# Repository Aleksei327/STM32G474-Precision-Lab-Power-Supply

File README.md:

# Precision Programmable Laboratory Power Supply

[Русская версия](README.ru.md)

A hardware development project for a galvanically isolated, fully programmable laboratory power supply. The design combines a tracking synchronous buck preregulator with a fast linear post-regulator to provide high efficiency without giving up low output noise.

> **Development status (November 2026):** both boards are etched, assembled and powered up, and the device runs on bring-up firmware. Verified on the bench so far: the auxiliary rails, the linear post-regulator and the synchronous buck without load. Tests under load in amps, the current limit and calibration are still ahead, so the specification table below lists design targets; measured values are in [First measurements](#first-measurements). The KiCad sources published here are the August 2026 revision — fixes found during bring-up are not merged yet.

*The assembled boards on the bench: main board, auxiliary flyback board, and the display on the diagnostics page of the bring-up firmware (55 V input switched off for the photo).*

## Target specifications

| Parameter | Target / current design |
| --- | --- |
| Output voltage | 0–50 V programmable; expected practical lower limit approximately 20–50 mV |
| Voltage setting increment | approximately 0.84 mV; 1 mV user step |
| Current setting increment | 1 mA in firmware |
| Output ripple | no more than 1 mV target |
| Present transformer capability | approximately 5–6 A continuous, 8 A peak — the limiting element today |
| Pass-element thermal budget | 7 A continuous with the current heatsink and a silicone insulator; 10 A in short bursts under NTC foldback |
| Power-stage design target | up to 10 A after the transformer rewind (a mica insulator is then required on the pass FET) |
| Operating modes | CV, digital CC, programmable foldback, controlled output ramps |
| Controller | STM32G474 |
| Voltage reference and DAC | REF5025 + 16-bit DAC8830 |
| Voltage/current monitor | 20-bit INA228 with a Kelvin-connected 10 mΩ shunt |

## First measurements

Bring-up results from 9 November 2026, taken with bring-up firmware and before any calibration.

| Test | Result |
| --- | --- |
| Linear stage, 10.000 V setpoint into 1.5 kΩ | 10.088 V on the INA228, drift within ±2 mV over one minute; the +0.9 % offset is the uncalibrated reference |
| Zero setpoint | 0.003 V at the output |
| Buck stage, no load, 100 kHz, 55.6 V input | pass-FET drain voltage follows pulse length linearly from 12.5 V to 27.2 V |
| Buck switching node | clean rectangle, 58.8 V peak (about 3 V overshoot), no missed pulses |
| Buck no-load input power at 49 % pulse length | about 6.4 W, mostly inductor core loss — under investigation |

Not tested yet: load currents in amps, current metering scale, the tracking loop, current limit, short-circuit protection in operation, and output above 25 V.

## Full schematic

The schematic is an A1 sheet. Open the SVG directly for lossless zoom.

[Russian schematic](docs/images/lab-psu-schematic-ru.svg)

## Boards

Two home-etched single-sided boards: a main board of about 260 × 152 mm and an auxiliary flyback board that generates the +67 V / −5 V rails for the post-regulator. Connections that cannot be routed on one copper layer are made with 25 documented wire jumpers.

*Copper side of the etched and assembled main board.*

[More views, layout details and the conventions used → PCB page](docs/pcb.md)

## How it works

The mains front end is based on a modified 500 W ATX supply. Its active PFC stage creates an approximately 380 V DC bus, followed by a two-switch forward converter that provides galvanic isolation and an approximately 55 V secondary rail.

An STM32G474 controls a synchronous buck stage through HRTIM. The buck output tracks the requested output voltage while maintaining only about 2–2.5 V across the linear pass MOSFET. A damped C–L–C filter attenuates switching components before the OPA454-based linear post-regulator removes the remaining ripple.

A 16-bit DAC8830 and REF5025 establish the voltage setpoint. An INA228 measures terminal voltage and shunt current; firmware implements the programmable current limit and foldback characteristic. Fast short-circuit interception does not depend on that digital loop: the STM32 analog front end drives the hardware comparator and HRTIM break input, while firmware simultaneously clears the voltage DAC and opens the output relay.

The output stage also includes reverse-polarity detection, external-voltage detection before relay closure, overvoltage protection, backfeed supervision, a fuse, surge clamps, thermal monitoring, and an independent thermal relay interlock.

## Documentation

- [System architecture and protection design](docs/architecture.md)
- [Auxiliary +67 V / −5 V flyback converter](docs/auxiliary-flyback.md)
- [PCB design and boards](docs/pcb.md)
- [Русская техническая документация](README.ru.md)

## Hardware sources

The complete KiCad 10 project is in [`hardware/`](hardware/README.md): schematic, layout, the project footprint library, hand-written 3D models with the Python scripts that generate them, and the SKiDL script the netlist is built from.

⚠️ The boards are drawn for home etching: **every drill hole in the file is a 0.6 mm pilot** that is opened up by hand afterwards. Restore the real diameters before sending these files to a fab.

## License and reuse

The documentation, the schematic and the hardware design files are published under [CC BY-NC-ND 4.0](LICENSE): read them, study them, share them with attribution, but no commercial use and no publishing of modified versions. **Building a single unit for your own private use is explicitly permitted** — the exact terms are in [NOTICE.md](NOTICE.md).

**The firmware is not published.** The hardware does not run without it, so if you build this board the control software is yours to write. Firmware and a video of the working device will follow once the hardware has been built and tested.

## Author

Aleksei Subbotin — embedded electronics and power control, France / remote. Open to freelance and contract work: [github.com/Aleksei327](https://github.com/Aleksei327) · <alsubfr@hotmail.com>

## Safety

This project contains rectified mains and an approximately 380 V DC bus. It is an engineering prototype, not a certified product. Construction and testing require appropriate isolation, current limiting, discharge procedures, protective equipment, and experience with lethal-voltage power electronics.

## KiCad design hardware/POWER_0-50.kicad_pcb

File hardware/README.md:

# Hardware sources

[Русская версия](README.ru.md) · [Back to the project overview](../README.md)

KiCad 10 project for the 0–50 V precision laboratory power supply. Open `POWER_0-50.kicad_pro`; the project-local footprint library resolves through `${KIPRJMOD}`, so no global library setup is needed.

> **Work in progress, published as-is.** The schematic and the layout are complete for this revision, but no board has been built or tested. Expect to find mistakes, and read [`docs/pcb.md`](../docs/pcb.md) before reusing anything — in particular the 0.6 mm pilot-hole convention, which will ruin a fab order if left as it is.

## Files

| Path | What it is |
| --- | --- |
| `POWER_0-50.kicad_sch` | schematic, single sheet (A1) |
| `POWER_0-50.kicad_pcb` | layout: 2 boards, 207 footprints, single-sided copper plus wire jumpers |
| `Library.pretty/` | 21 project footprints (see below) |
| `Library.3dshapes/` | 16 hand-written 3D models plus the Python generators that produce them |
| `netlist/lab_psu_skidl.py` | SKiDL script that generates the netlist — the electrical source of truth |
| `netlist/lab_psu.net` | generated netlist, the reference the schematic and the PCB are checked against |
| `netlist/lab_psu_chips.kicad_sym` | symbols for the parts KiCad does not ship |
| `jumper-wires.txt` | assembly list of the 25 wire jumpers with coordinates and lengths |

## Project footprint library

Everything that is either not in the stock libraries or had to be adapted for hand assembly:

- **Modules:** WeAct STM32G474CEU6 core board, Adafruit-style INA228 breakout (its screw terminal shares pad numbers with the header pins, so a wire can be soldered to whichever is convenient).
- **HSOP-8 with exposed pad, hand-solder pads:** `UCC27211` (EP → GND), `MP9486A` (EP → GND), `OPA454` (**EP → V− = −5 V**, not ground — see the datasheet).
- **Mechanical parts as real footprints:** three heatsinks, the constantan shunt staple, the flyback transformer on its measured bobbin, relays, the wound toroids, a THT NTC.
- Wide-pad SOIC-8/16 variants and various through-hole passives for parts that dissipate more than an SMD package can take.

## 3D models

KiCad 10 ships only STEP models, and several stock footprints in this project reference STEP files that are not in the distribution at all. The missing parts were modelled by hand as VRML and are generated by the scripts in `Library.3dshapes/_generators/`:

```
python wrlgen.py    # primitives, heatsinks, wound toroids, relays
python wrlgen2.py   # module boards, flyback transformer, NTC, SMD inductor
python wrlgen3.py   # fuse holder, connectors, shunt staple
python stand.py R21,J6   # preview rig: copies the board, keeps only the named parts
```

Two things worth knowing if you edit them: one VRML unit is 2.54 mm, the model Y axis is the negative of the board Y axis, and **KiCad's VRML loader does not draw the built-in `Cylinder` primitive at all** — every round shape here is an explicit `IndexedFaceSet` mesh.

## Netlist generator

The schematic was not drawn by hand first: `netlist/lab_psu_skidl.py` builds the circuit in SKiDL, and the resulting netlist is the reference that both the schematic and the board are verified against. If you change the circuit there, note that new parts must be appended at the **end** of the script — inserting them in the middle renumbers every later reference designator and silently desynchronises the board.

## Firmware

Not included. The firmware is not published yet, and this hardware does not operate without it — see [NOTICE.md](../NOTICE.md).

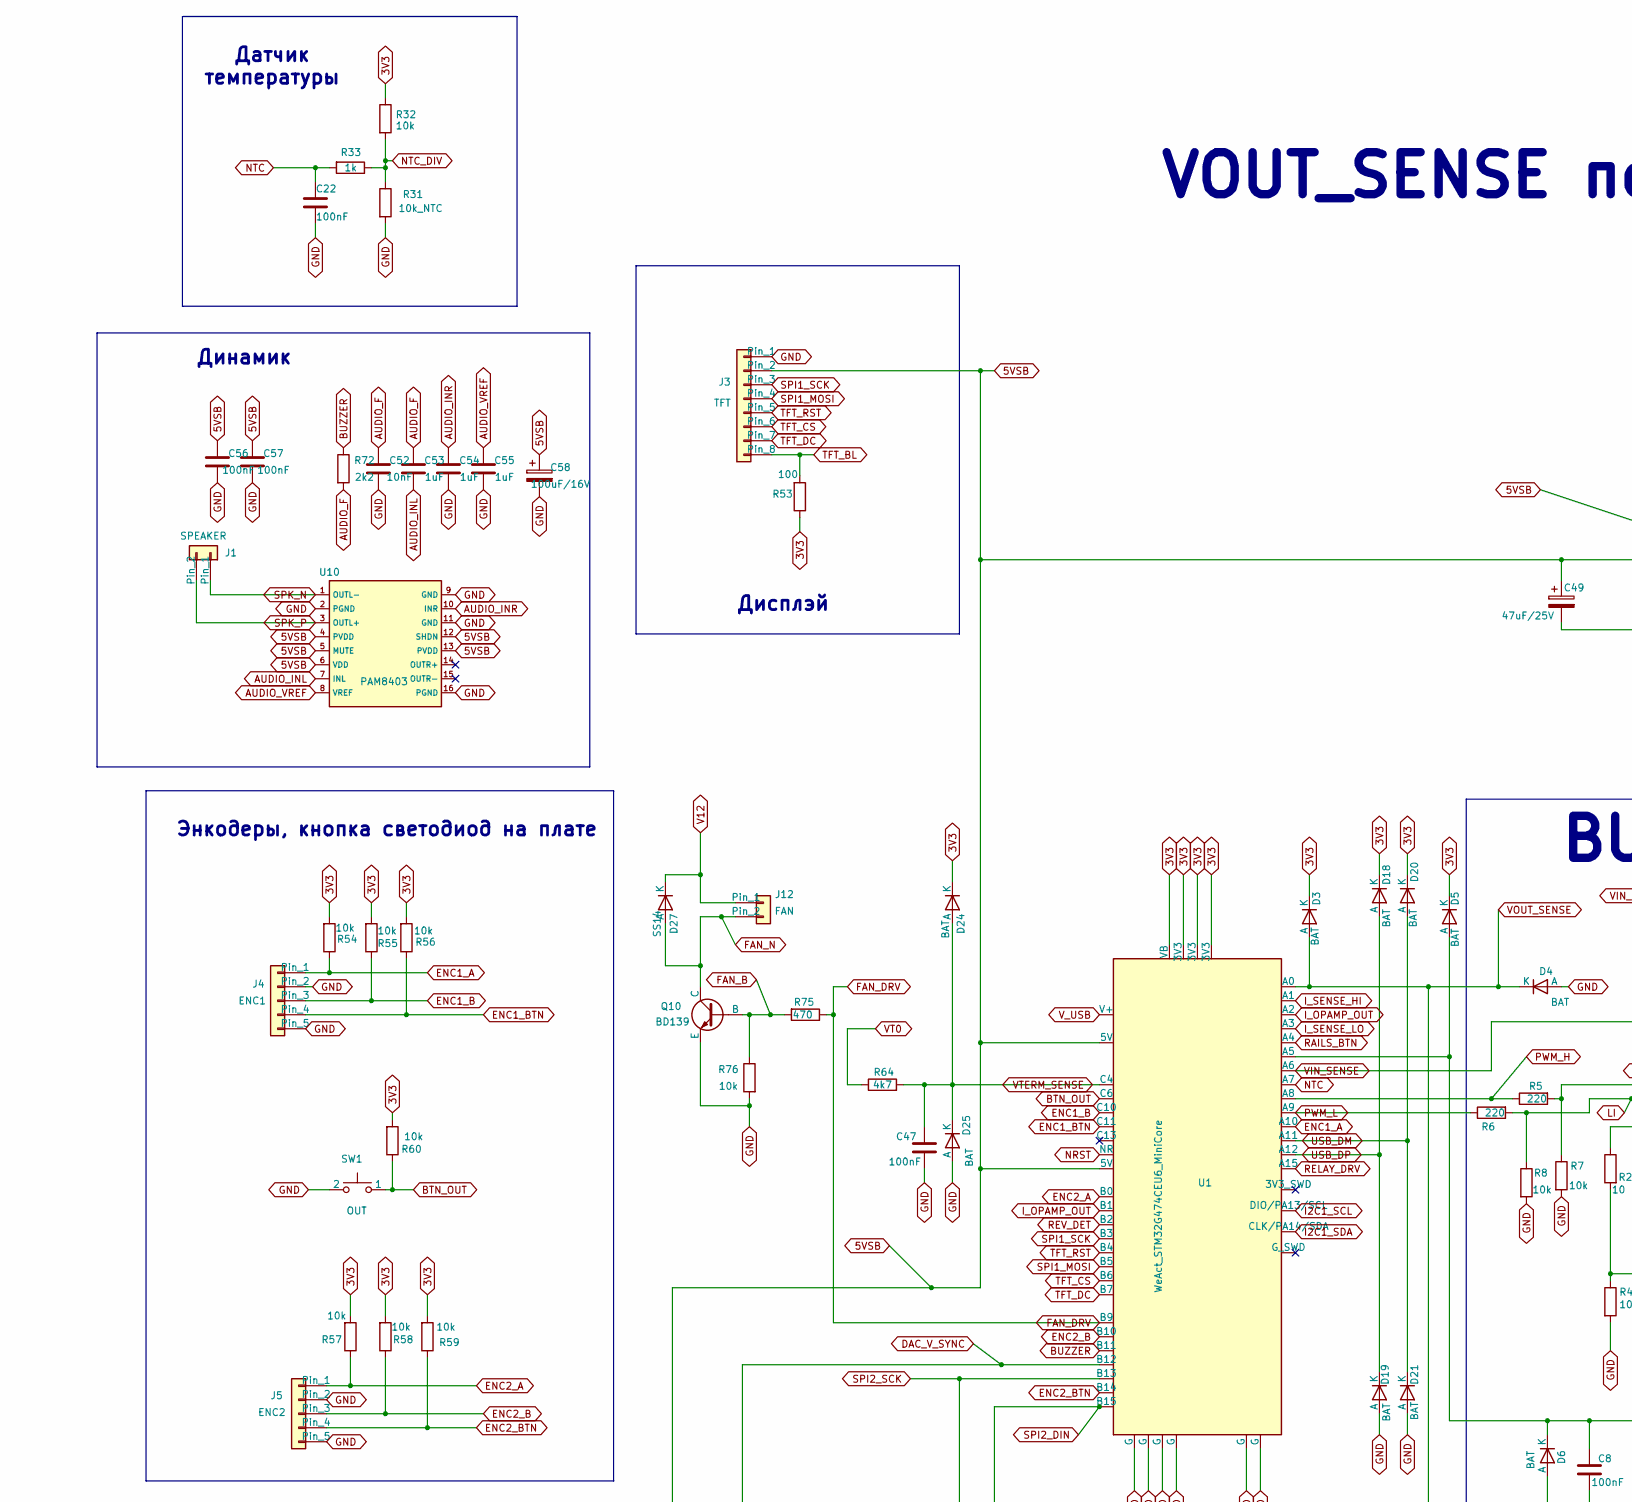
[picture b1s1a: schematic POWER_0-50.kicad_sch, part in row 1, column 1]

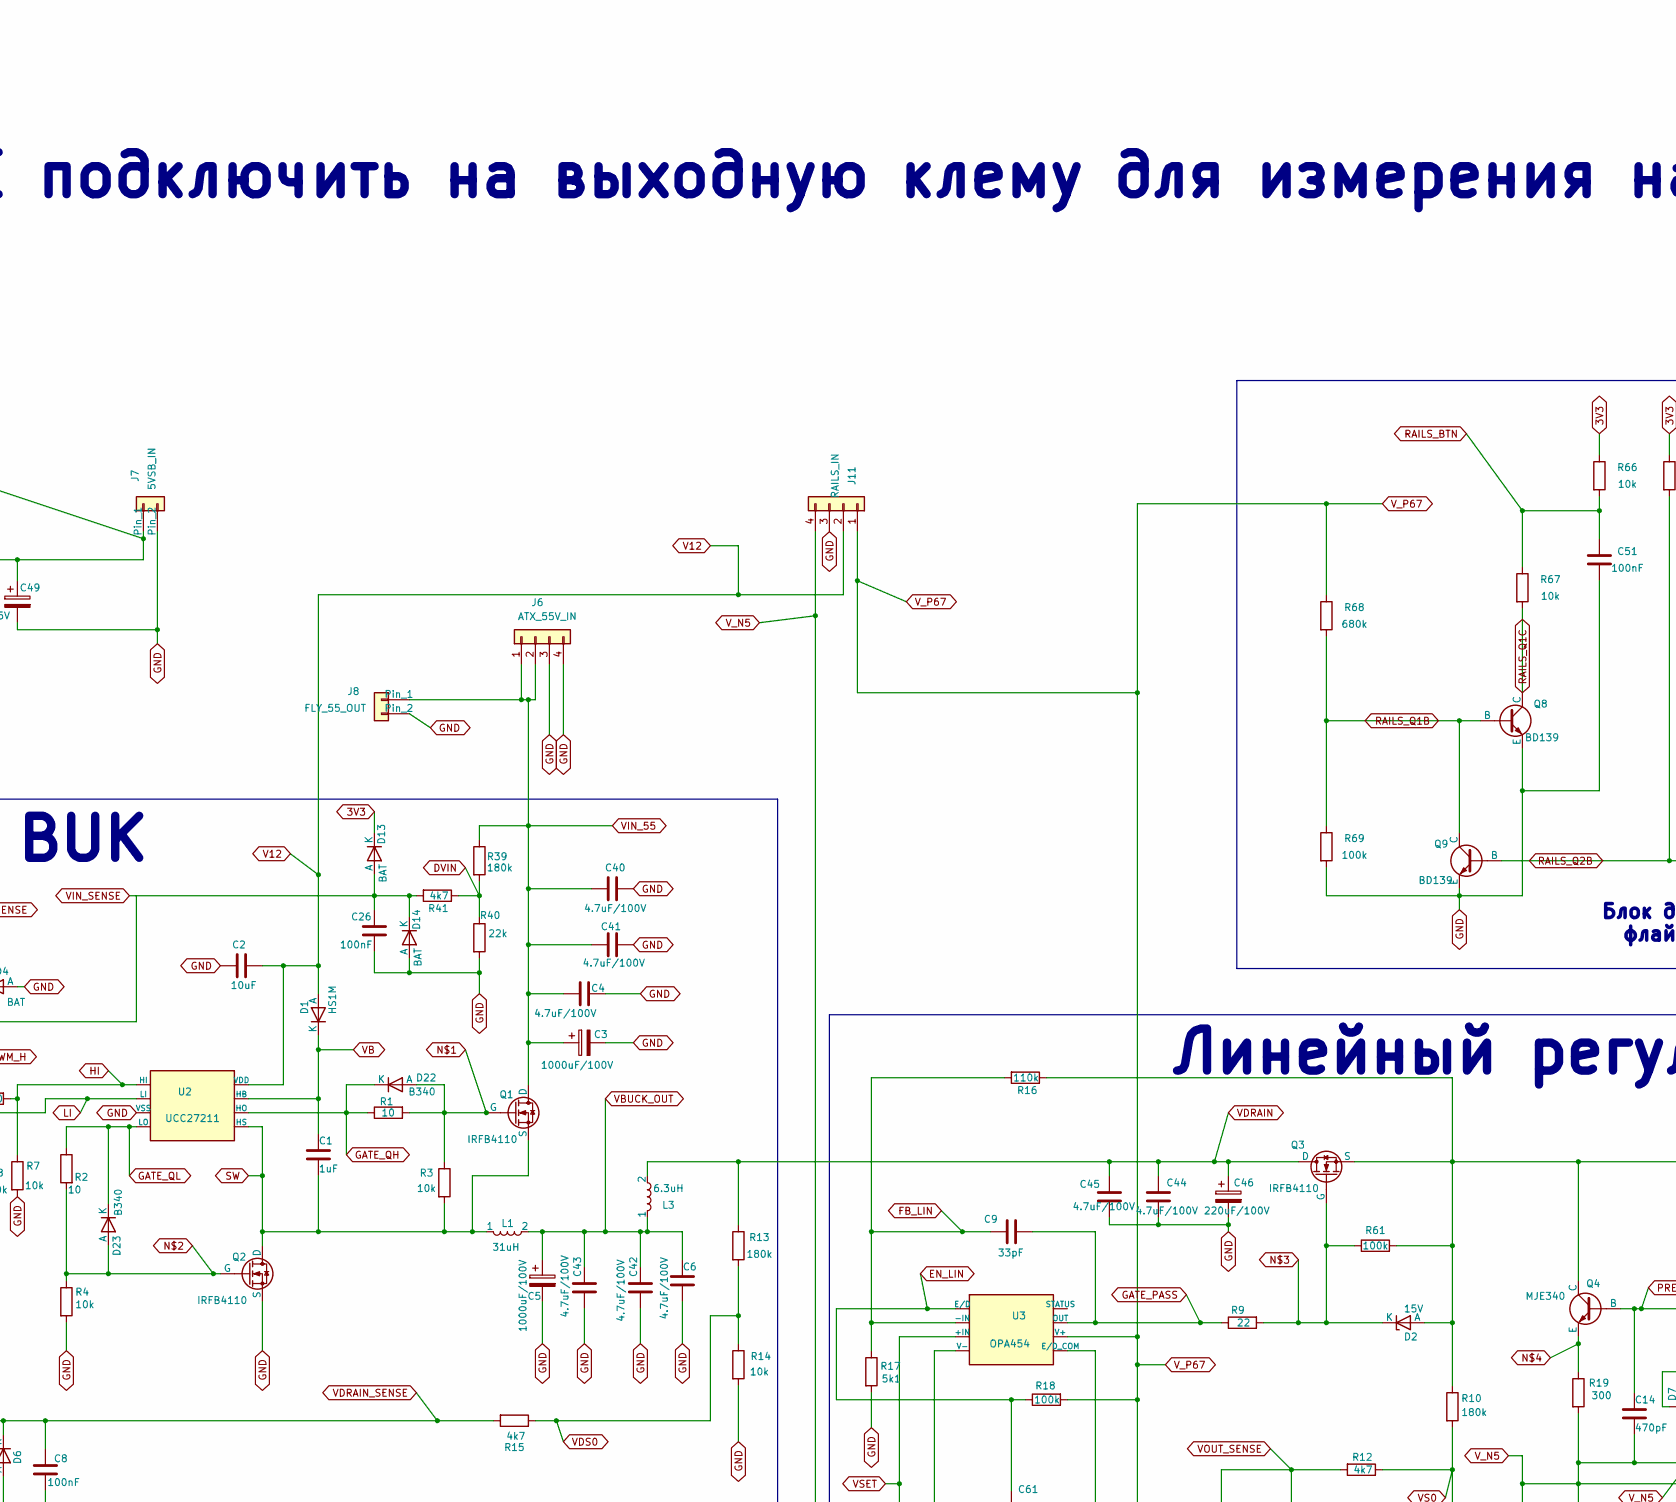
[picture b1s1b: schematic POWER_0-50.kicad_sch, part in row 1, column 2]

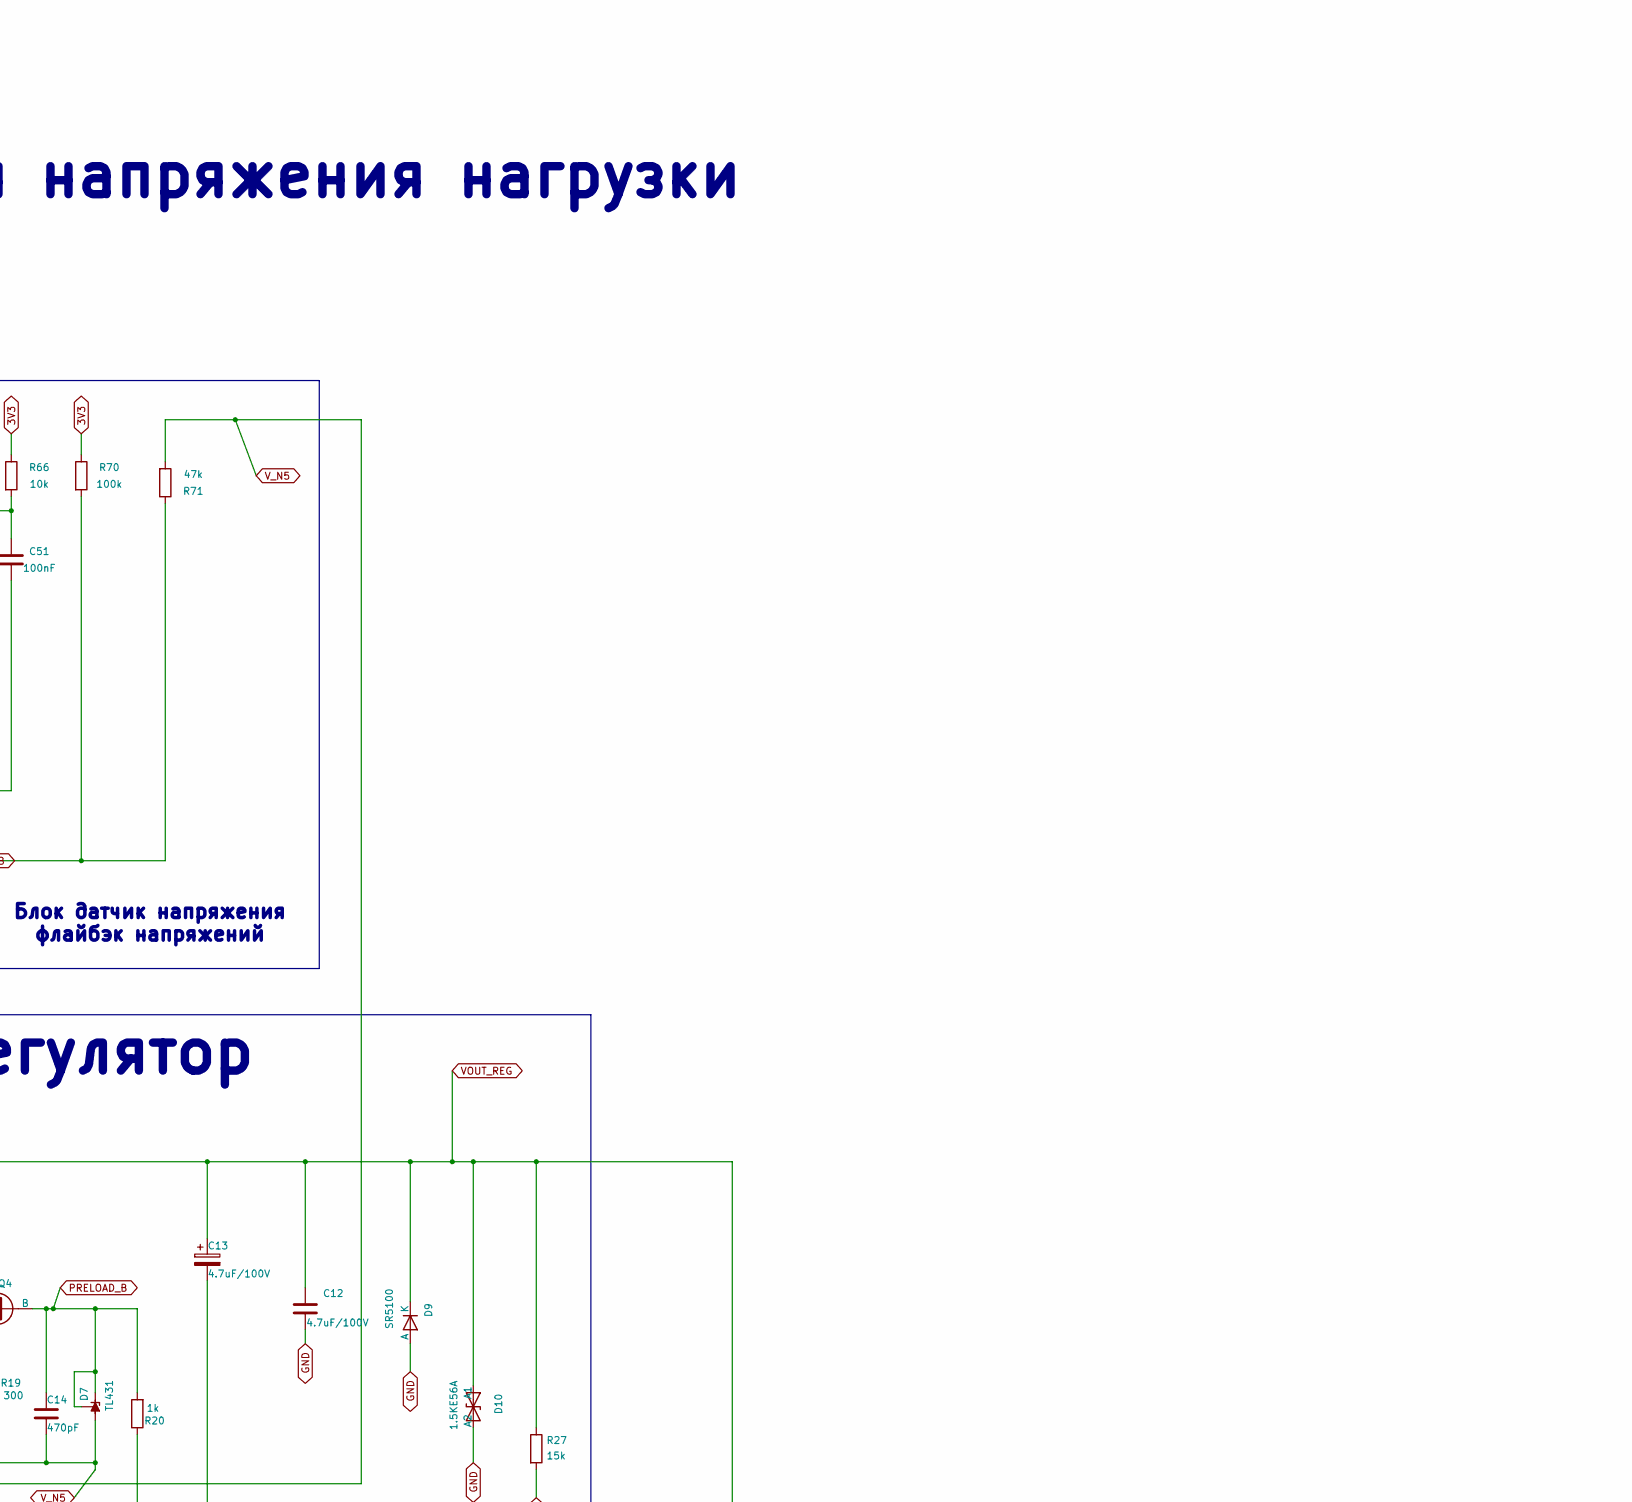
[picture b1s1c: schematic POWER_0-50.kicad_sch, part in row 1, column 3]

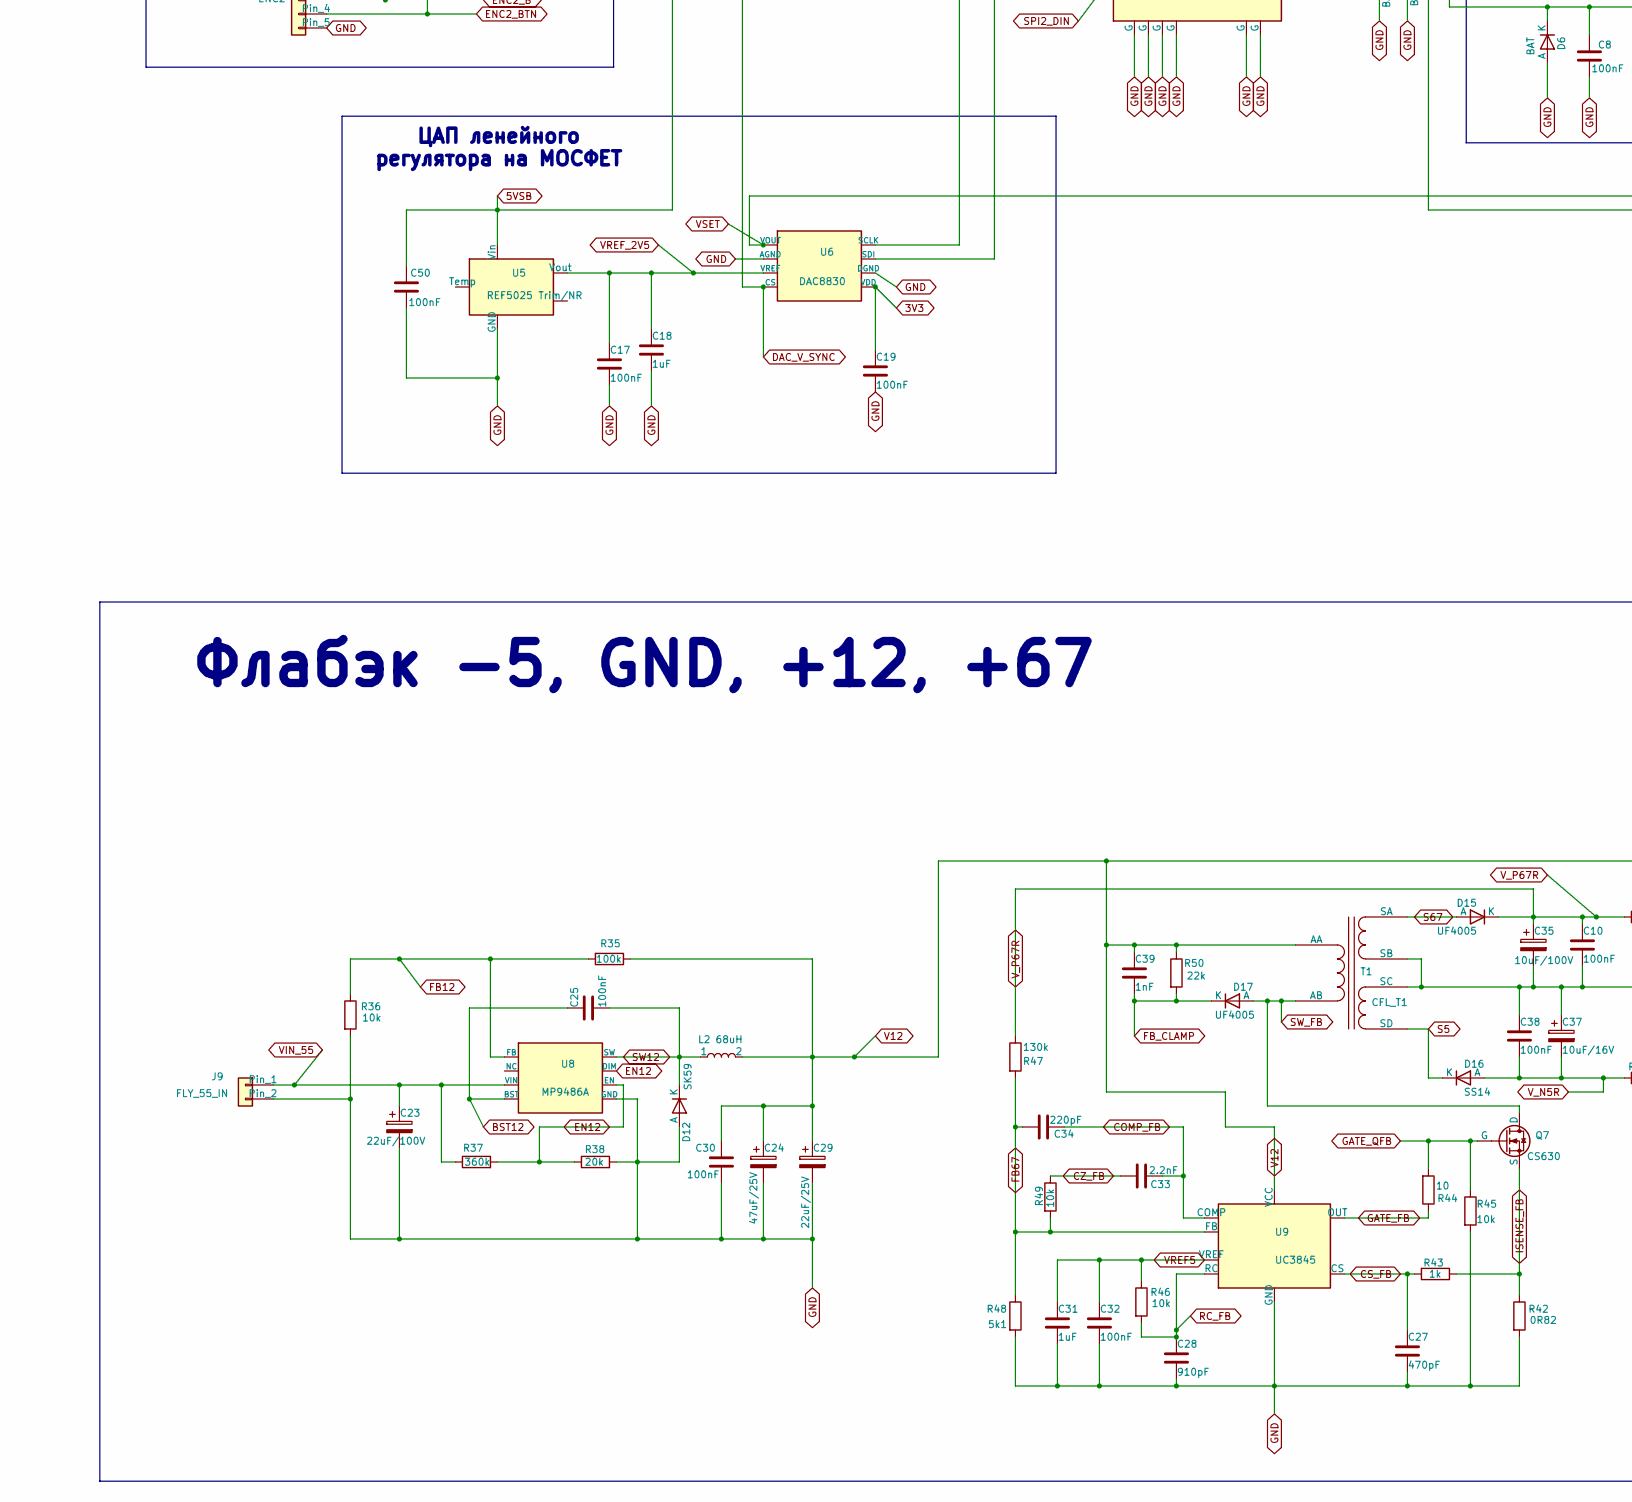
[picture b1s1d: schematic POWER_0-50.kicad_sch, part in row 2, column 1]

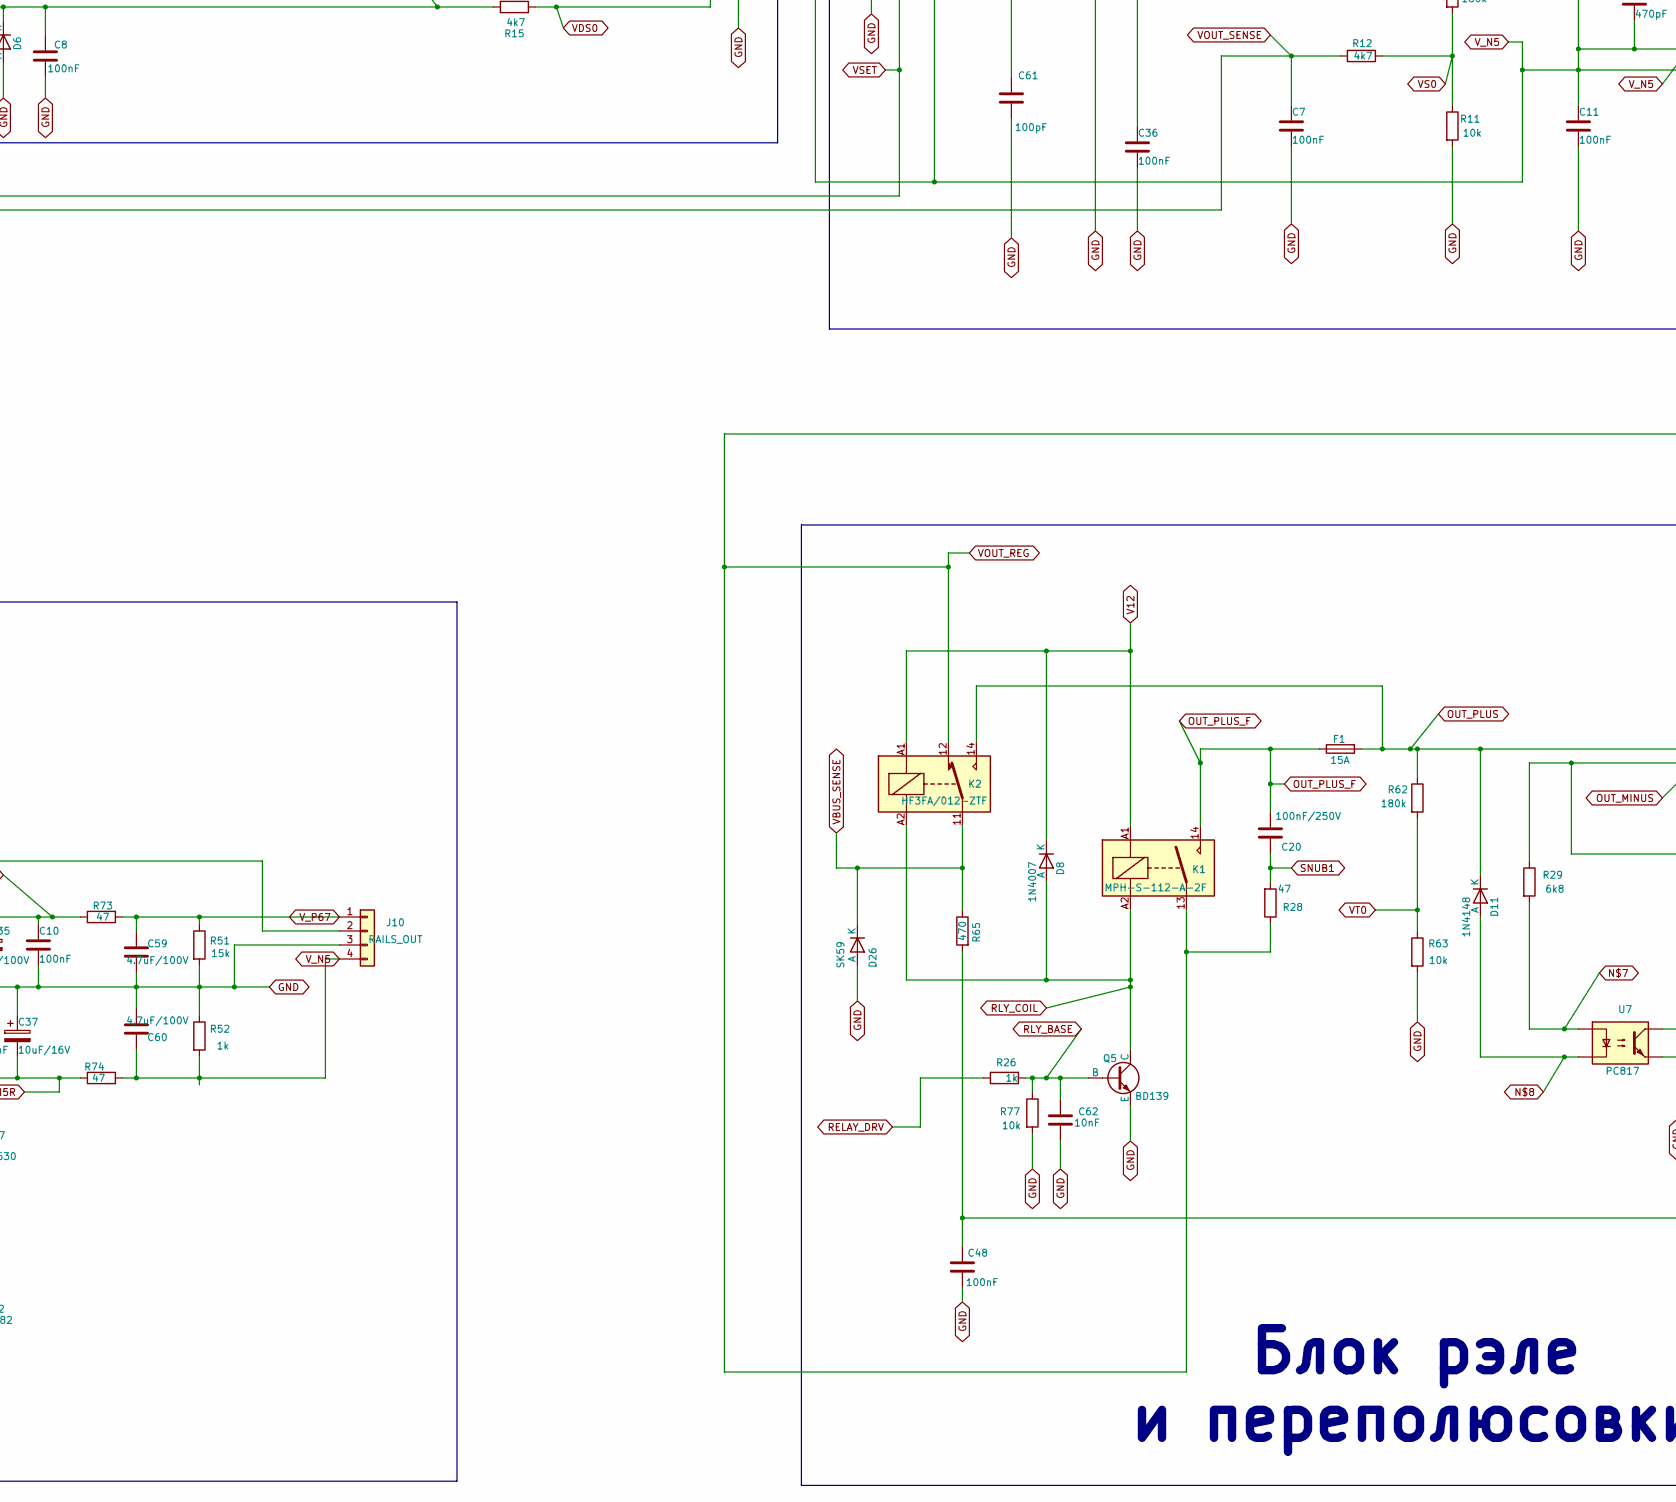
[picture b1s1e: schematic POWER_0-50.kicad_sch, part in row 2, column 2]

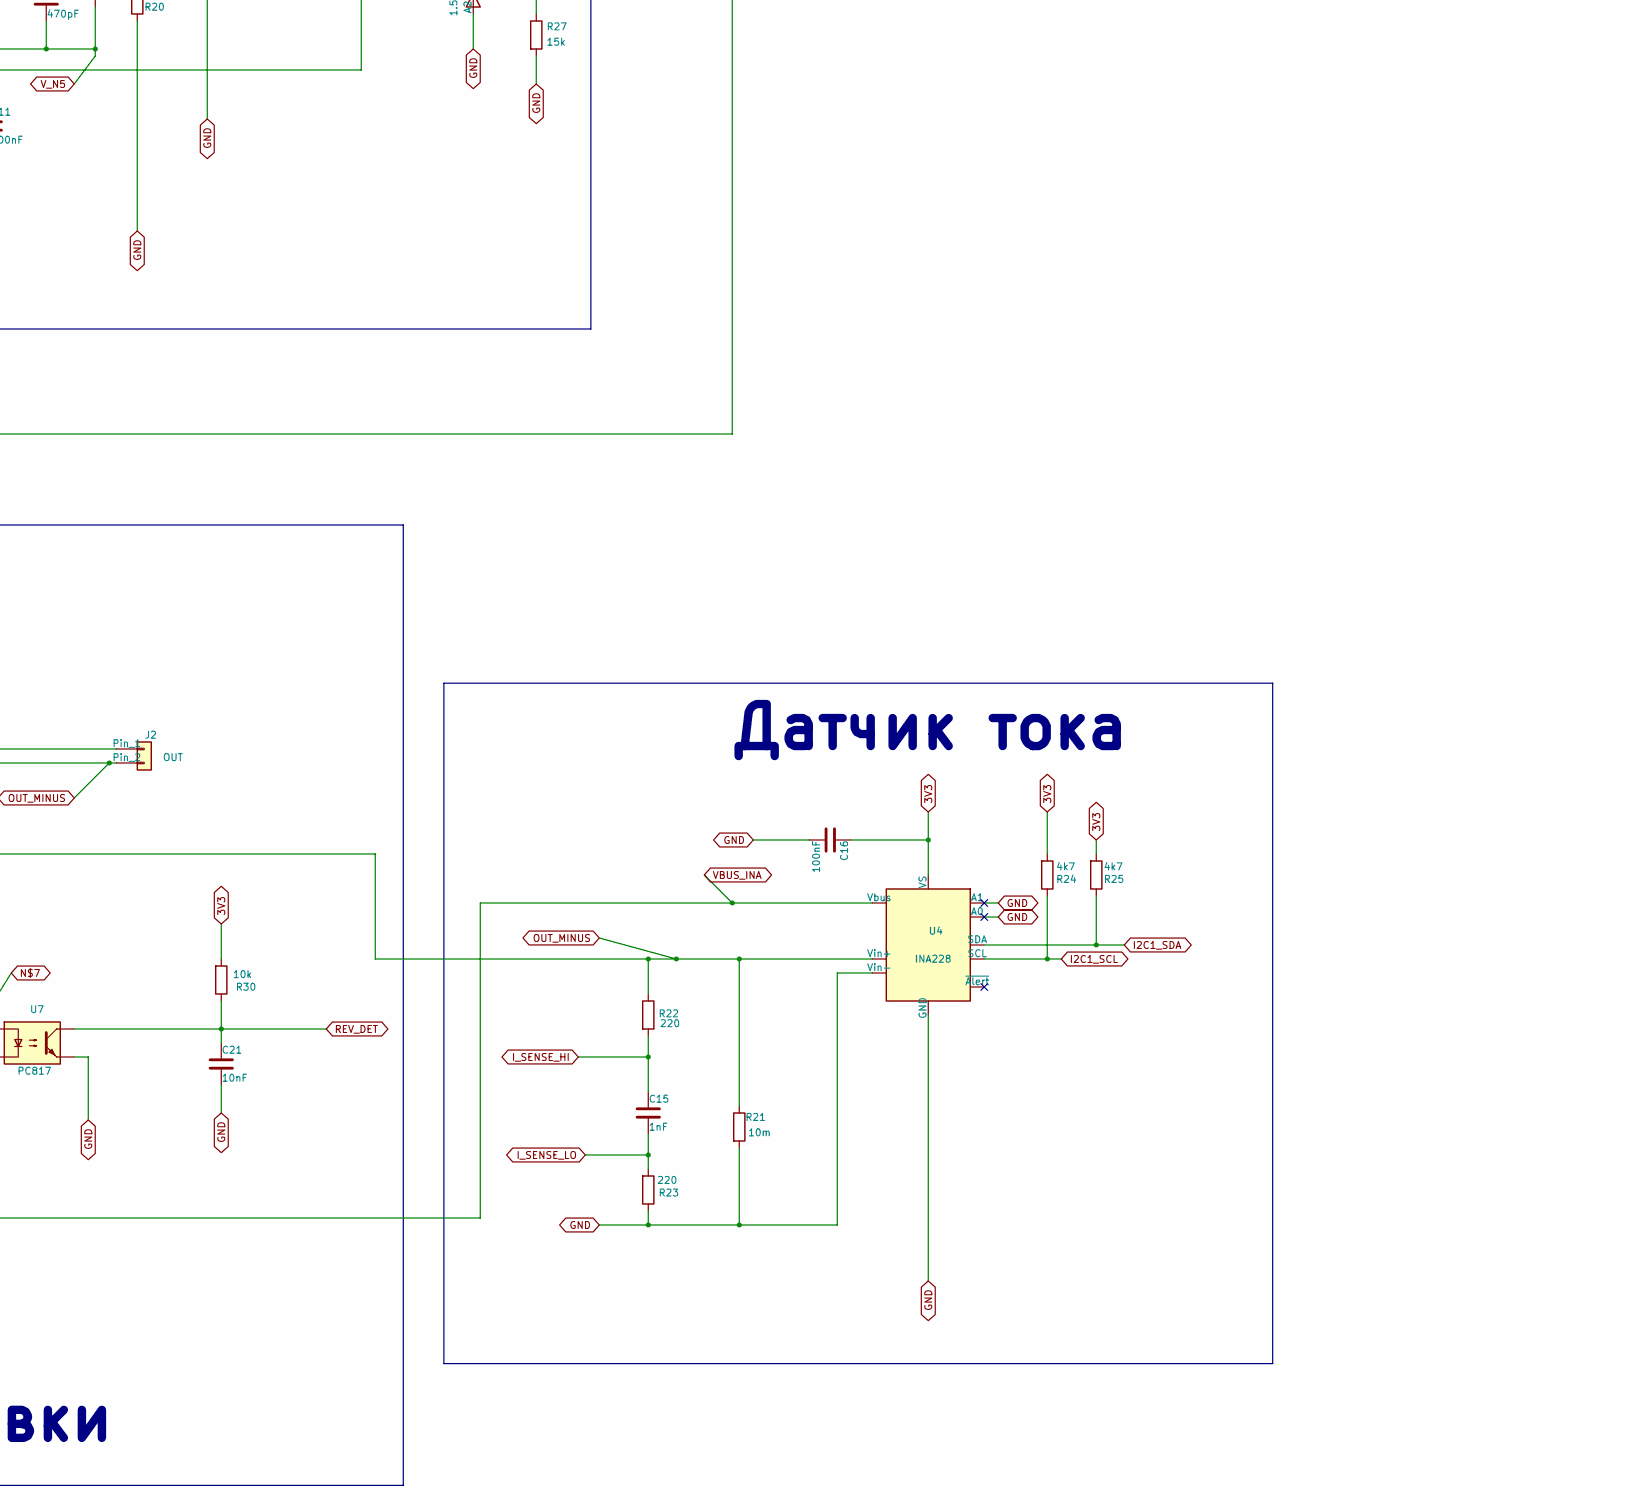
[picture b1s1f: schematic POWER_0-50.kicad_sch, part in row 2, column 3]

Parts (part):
C1, C18, C31, C53, C54, C55: 1uF; C_1206_3216Metric
C2: 10uF; C_1206_3216Metric
C3, C5: 1000uF/100V; CP_Radial_D18.0mm_P7.50mm
C4, C6, C12, C13, C40, C41, C42, C43, C44, C45, C59, C60: 4.7uF/100V; C_1206_3216Metric
C7, C8, C10, C11, C16, C17, C19, C22, C25, C26, C30, C32, C36, C38, C47, C48, C50, C51, C56, C57: 100nF; C_1206_3216Metric
C9: 33pF; C_1206_3216Metric
C14, C27: 470pF; C_1206_3216Metric
C15, C39: 1nF; C_1206_3216Metric
C20: 100nF/250V; C_1206_3216Metric
C21, C52, C62: 10nF; C_1206_3216Metric
C23: 22uF/100V; CP_Radial_D10.0mm_P5.00mm
C24, C49: 47uF/25V; CP_Radial_D10.0mm_P5.00mm
C28: 910pF; C_1206_3216Metric
C29: 22uF/25V; CP_Radial_D10.0mm_P5.00mm
C33: 2.2nF; C_1206_3216Metric
C34: 220pF; C_1206_3216Metric
C35: 10uF/100V; CP_Radial_D10.0mm_P5.00mm
C37: 10uF/16V; CP_Radial_D10.0mm_P5.00mm
C46: 220uF/100V; CP_Radial_D13.0mm_P5.00mm
C58: 100uF/16V; CP_Radial_D10.0mm_P5.00mm
C61: 100pF; C_1206_3216Metric
D1: HS1M; D_SMA
D2: 15V; D_DO-35_SOD27_P10.16mm_Horizontal
D3, D4, D5, D6, D13, D14, D18, D19, D20, D21, D24, D25: BAT; D_SOD-323_HandSolder
D7: TL431; TO-126-3_Vertical
D8: 1N4007; D_DO-201AD_P15.24mm_Horizontal
D9: SR5100; D_DO-201AD_P15.24mm_Horizontal
D10: 1.5KE56A; D_DO-201AD_P15.24mm_Horizontal
D11: 1N4148; D_DO-35_SOD27_P10.16mm_Horizontal
D12, D26: SK59; D_SMC
D15, D17: UF4005; D_DO-41_SOD81_P10.16mm_Horizontal
D16, D27: SS14; D_SMA
D22, D23: B340; D_SMC
F1: 15A; Fuseholder_Clip-5x20mm_Littelfuse_100_Inline_P20.50x4.60mm_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
J1: SPEAKER; PinHeader_1x02_P2.54mm_Vertical
J2: OUT; TerminalBlock_MaiXu_MX126-5.0-02P_1x02_P5.00mm
J3: TFT; PinHeader_1x08_P2.54mm_Vertical
J4: ENC1; PinHeader_1x05_P2.54mm_Vertical
J5: ENC2; PinHeader_1x05_P2.54mm_Vertical
J6: ATX_55V_IN; Molex_KK-396_A-41791-0004_1x04_P3.96mm_Vertical
J7: 5VSB_IN; PinHeader_1x02_P2.54mm_Vertical
J8: FLY_55_OUT; PinHeader_1x02_P2.54mm_Vertical
J9: FLY_55_IN; Conn_FLY55_JST_EH_1x03_P2.5_pins13
J10: RAILS_OUT; Conn_RAILS_1x04_P2.54_D0.6
J11: RAILS_IN; PinSocket_1x04_P2.54mm_Vertical
J12: FAN; PinHeader_1x02_P2.54mm_Vertical
K1: MPH-S-112-A-2F; Relay_MPH_1A
K2: HF3FA/012-ZTF; Relay_HF3FA_1C
L1: 31uH; L_Toroid_Vertical_Core25x10mm_P14.00mm_D1.8mm
L2: 68uH; L_SMD_15x15mm
L3: 6.3uH; L_Toroid_Vertical_Core21x7mm_P10.00mm_D2.0mm
Q1, Q2, Q3: IRFB4110; TO-220-3_Vertical
Q4: MJE340; TO-126-3_Vertical
Q5, Q8, Q9, Q10: BD139; TO-126-3_Vertical
Q7: CS630; TO-252-2
R1, R2: 10; R_2512_6332Metric
R3, R4, R7, R8, R11, R14, R30, R32, R36, R45, R46, R49, R54, R55, R56, R57, R58, R59, R60, R63, R66, R67, R76, R77: 10k; R_1206_3216Metric
R5, R6, R22, R23: 220; R_1206_3216Metric
R9: 22; R_Axial_DIN0207_L6.3mm_D2.5mm_P10.16mm_Horizontal
R10, R13, R39, R62: 180k; R_1206_3216Metric
R12, R15, R24, R25, R41, R64: 4k7; R_1206_3216Metric
R16: 110k; R_0805_2012Metric
R17: 5k1; R_0805_2012Metric
R18, R35, R61, R69, R70: 100k; R_1206_3216Metric
R19: 300; R_1206_3216Metric
R20, R26, R33, R43, R52: 1k; R_1206_3216Metric
R21: 10m; Shunt_Constantan_Staple_P20mm
R27, R51: 15k; R_Axial_DIN0207_L6.3mm_D2.5mm_P10.16mm_Horizontal
R28: 47; R_Axial_DIN0207_L6.3mm_D2.5mm_P10.16mm_Horizontal
R29: 6k8; R_Axial_DIN0207_L6.3mm_D2.5mm_P10.16mm_Horizontal
R31: 10k_NTC; NTC_THT_P7.00mm_Pad2.0mm_D0.6mm
R37: 360k; R_1206_3216Metric
R38: 20k; R_1206_3216Metric
R40, R50: 22k; R_1206_3216Metric
R42: 0R82; R_Axial_DIN0411_L9.9mm_D3.6mm_P12.70mm_Horizontal
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
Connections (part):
3V3: C16.1, C19.1, D3.1 (K), D5.1 (K), D13.1 (K), D18.1 (K), D20.1 (K), D24.1 (K), R24.2, R25.2, R30.2, R32.1, R53.1, R54.2, R55.2, R56.2, R57.2, R58.2, R59.2, R60.2, R66.1, R70.1, U1.3 (3V3), U1.4 (3V3), U1.22 (VB), U1.23 (3V3), U4.6 (VS), U6.8 (VDD)
5VSB: C49.1, C50.1, C56.1, C57.1, C58.1, J3.2, J7.1, U1.27 (5V), U1.28 (5V), U5.2 (Vin), U10.4 (PVDD), U10.5 (MUTE), U10.6 (VDD), U10.12 (SHDN), U10.13 (PVDD)
AUDIO_F: C52.1, C53.1, R72.2
AUDIO_INL: C53.2, U10.7 (INL)
AUDIO_INR: C54.1, U10.10 (INR)
AUDIO_VREF: C55.1, U10.8 (VREF)
BST12: C25.1, U8.4 (BST)
BTN_OUT: R60.1, SW1.1, U1.33 (C6)
BUZZER: R72.1, U1.5 (B11)
COMP_FB: C33.1, C34.1, U9.1 (COMP)
CS_FB: C27.1, R43.2, U9.3 (CS)
CZ_FB: C33.2, R49.1
DAC_V_SYNC: U1.29 (B12), U6.4 (CS)
DVIN: R39.2, R40.1, R41.1
EN12: R37.2, R38.1, U8.6 (DIM), U8.7 (EN)
ENC1_A: J4.1, R54.1, U1.36 (A10)
ENC1_B: J4.3, R55.1, U1.40 (C10)
ENC1_BTN: J4.4, R56.1, U1.41 (C11)
ENC2_A: J5.1, R57.1, U1.10 (B0)
ENC2_B: J5.3, R58.1, U1.6 (B10)
ENC2_BTN: J5.4, R59.1, U1.31 (B14)
EN_LIN: C61.1, R18.1, U3.8 (E/D)
FAN_B: Q10.3 (B), R75.2, R76.1
FAN_DRV: R75.1, U1.47 (B9)
FAN_N: D27.2 (A), J12.2, Q10.2 (C)
FB12: R35.2, R36.1, U8.1 (FB)
FB67: C34.2, R47.2, R48.1, R49.2, U9.2 (FB)
FB_CLAMP: C39.2, D17.1 (K), R50.2
FB_LIN: C9.2, R16.2, R17.1, U3.2 (-IN)
GATE_FB: R44.1, U9.6 (OUT)
GATE_PASS: C9.1, R9.1, U3.6 (OUT)
GATE_QFB: Q7.1 (G), R44.2, R45.1
GATE_QH: D22.1 (K), R1.1, U2.3 (HO)
GATE_QL: D23.1 (K), R2.1, U2.8 (LO)
GND: C2.2, C3.2, C4.2, C5.2, C6.2, C7.2, C8.2, C10.2, C11.2, C12.2, C13.2, C16.2, C17.2, C18.2, C19.2, C21.2, C22.2, C23.2, C24.2, C26.2, C27.2, C28.2, C29.2, C30.2, C31.2, C32.2, C35.2, C36.2, C37.1, C38.1, C40.2, C41.2, C42.2, C43.2, C44.2, C45.2, C46.2, C47.2, C48.2, C49.2, C50.2, C51.2, C52.2, C54.2, C55.2, C56.2, C57.2, C58.2, C59.2, C60.2, C61.2, C62.2, D4.2 (A), D6.2 (A), D9.2 (A), D10.2 (A2), D12.2 (A), D14.2 (A), D19.2 (A), D21.2 (A), D25.2 (A), D26.2 (A), J3.1, J4.2, J4.5, J5.2, J5.5, J6.3, J6.4, J7.2, J8.2, J9.2, J10.3, J11.3, Q2.3 (S), Q5.1 (E), Q8.1 (E), Q9.1 (E), Q10.1 (E), R4.2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
HI: R5.2, R7.1, U2.5 (HI)
I2C1_SCL: R24.1, U1.DIO (DIO/PA13/SCL), U4.5 (SCL)
I2C1_SDA: R25.1, U1.CLK (CLK/PA14/SDA), U4.4 (SDA)
ISENSE_FB: Q7.3 (S), R42.1, R43.1
I_OPAMP_OUT: U1.9 (B1), U1.17 (A2)
I_SENSE_HI: C15.1, R22.2, U1.18 (A1)
I_SENSE_LO: C15.2, R23.2, U1.16 (A3)
LI: R6.2, R8.1, U2.6 (LI)
unnamed: D22.2 (A), Q1.1 (G), R1.2, R3.1
unnamed: D23.2 (A), Q2.1 (G), R2.2, R4.1
unnamed: D2.1 (K), Q3.1 (G), R9.2, R61.1
unnamed: Q4.1 (E), R19.1
unnamed: R29.2, U7.1
unnamed: D11.2 (A), U7.2
NRST: U1.20 (NR)
NTC: C22.1, R33.2, U1.12 (A7)
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
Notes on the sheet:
VOUT_SENSE подключить на выходную клему для измерения напряжения нагрузки
Динамик
Флабэк -5, GND, +12, +67
Блок датчик напряжения флайбэк напряжений
Датчик температуры
Дисплэй
Линейный регулятор
ЦАП ленейного регулятора на МОСФЕТ
Блок рэле и переполюсовки
Датчик тока
BUK
Энкодеры, кнопка светодиод на плате

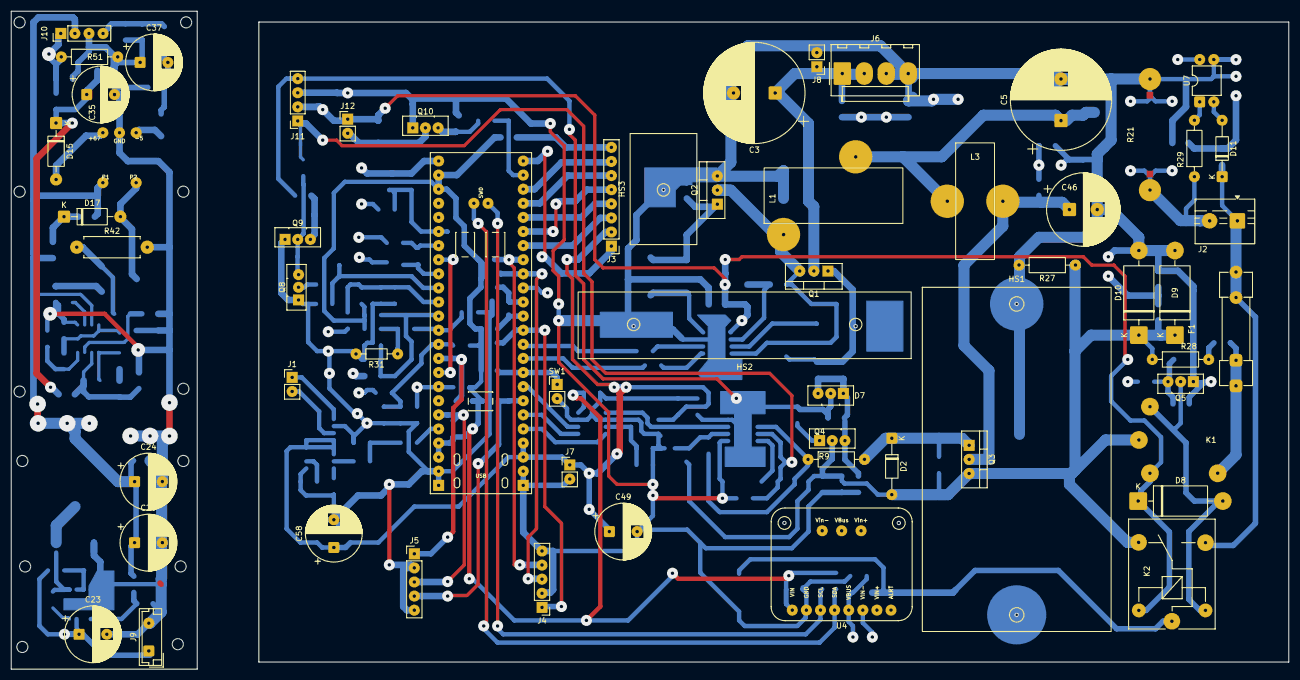
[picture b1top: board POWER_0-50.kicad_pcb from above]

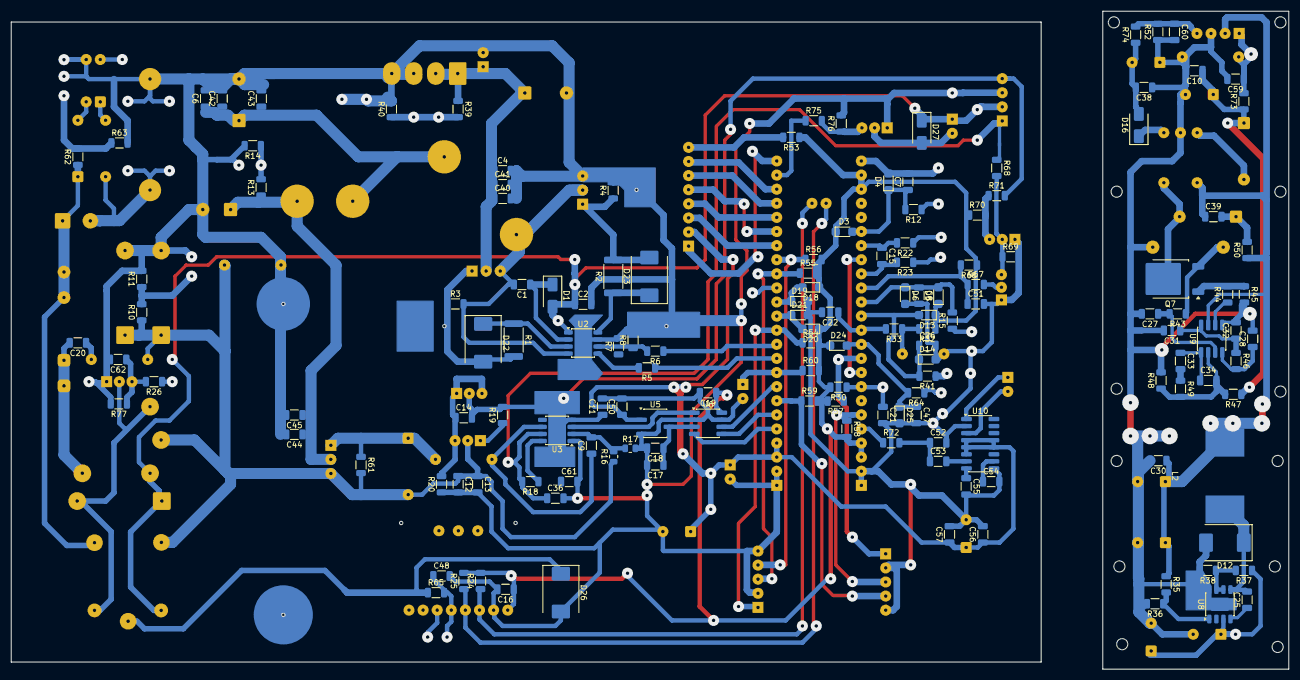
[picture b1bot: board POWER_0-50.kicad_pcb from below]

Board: 2 copper layers, 230.1 x 118.5 mm, 207 parts (148 on the bottom side), 106 nets.

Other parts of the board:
HS1: Heatsink_Amp_62x40x34
HS2: Heatsink_Profile_60mm
HS3: Heatsink_Profile_20mm
